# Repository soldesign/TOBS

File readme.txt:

Currently, 1.3 billion people live without access to electricity. Most of them are inhabitants of rural regions in developing south, that don’t have connection to the electricity grid. 
Fortunately, clean energy technologies have been reaching these people more and more in the past years. Mostly, but not only, in Bangladesh, a renewable energy revolution is taking place: the emergence of small scale solar-home-systems that supply electricity for lighting, cellphones and household appliances - in Bangladesh alone, there are already over 5 million solar-home-systems installed! These system feature a small PV panel with a charging controller and a battery (The solar home systems are usually financed with a micro loan from a microfinance institution, because its owner sometimes earn as little as one dollar per day).

To cut costs in these systems, lead-acid batteries are usually installed. Unfortunately, lead-acid batteries have a limited number of charge-discharge-cycles, much less than, for example, modern LIFEPO batteries. Also, they age quickly if they are discharged below around 40% of their capacity. This leads to many of the batteries breaking within 2 years or less, rendering the solar home systems unusable.

Moreover, as developing countries don’t have proficient infrastructure to dispose or recycle the lead-acid batteries, each failing battery leads to waste of resources and significant environmental pollution.

>lead acid batties are vulnurable to cycling often

How to solve the problem?

-retrofitting hybrid charge controller!

Using LIFEPO based batteries would significantly increase the solar home system’s lifetime­, as LIFEPO batteries are less affected by cycling compared to lead-acid batteries. However, initial high investment costs for LIFEPO batteries are often not feasible for developing markets. To get the best of both, a hybrid charge controller which supports a small lithium-ion battery and a bigger lead-acid battery simultaneously, would be ideal.

> LIFEPO batteries are better but too expensive 

A normal charge controller is responsible for monitoring the battery’s voltage and for controlling the charge and discharge cycle. In comparison, a hybrid charge controller would be able to switch between the two battery types, considering environmental factors, such as load current, solar irradiance and state of charge of both batteries. This will result in the li-ion battery having a smaller capacity, therefore cutting its cost. An algorithm would then only use the lead acid battery if the load is too big for the lithium ion battery to handle. For smaller loads and thus more cycles, the lithium ion battery would be used.

> lead acid battery will be cycled less often

Thus, the new hybrid charge controller aims to prolong the lifespan of millions of already existing lead acid batteries inside solar home systems by reducing sulfuration.

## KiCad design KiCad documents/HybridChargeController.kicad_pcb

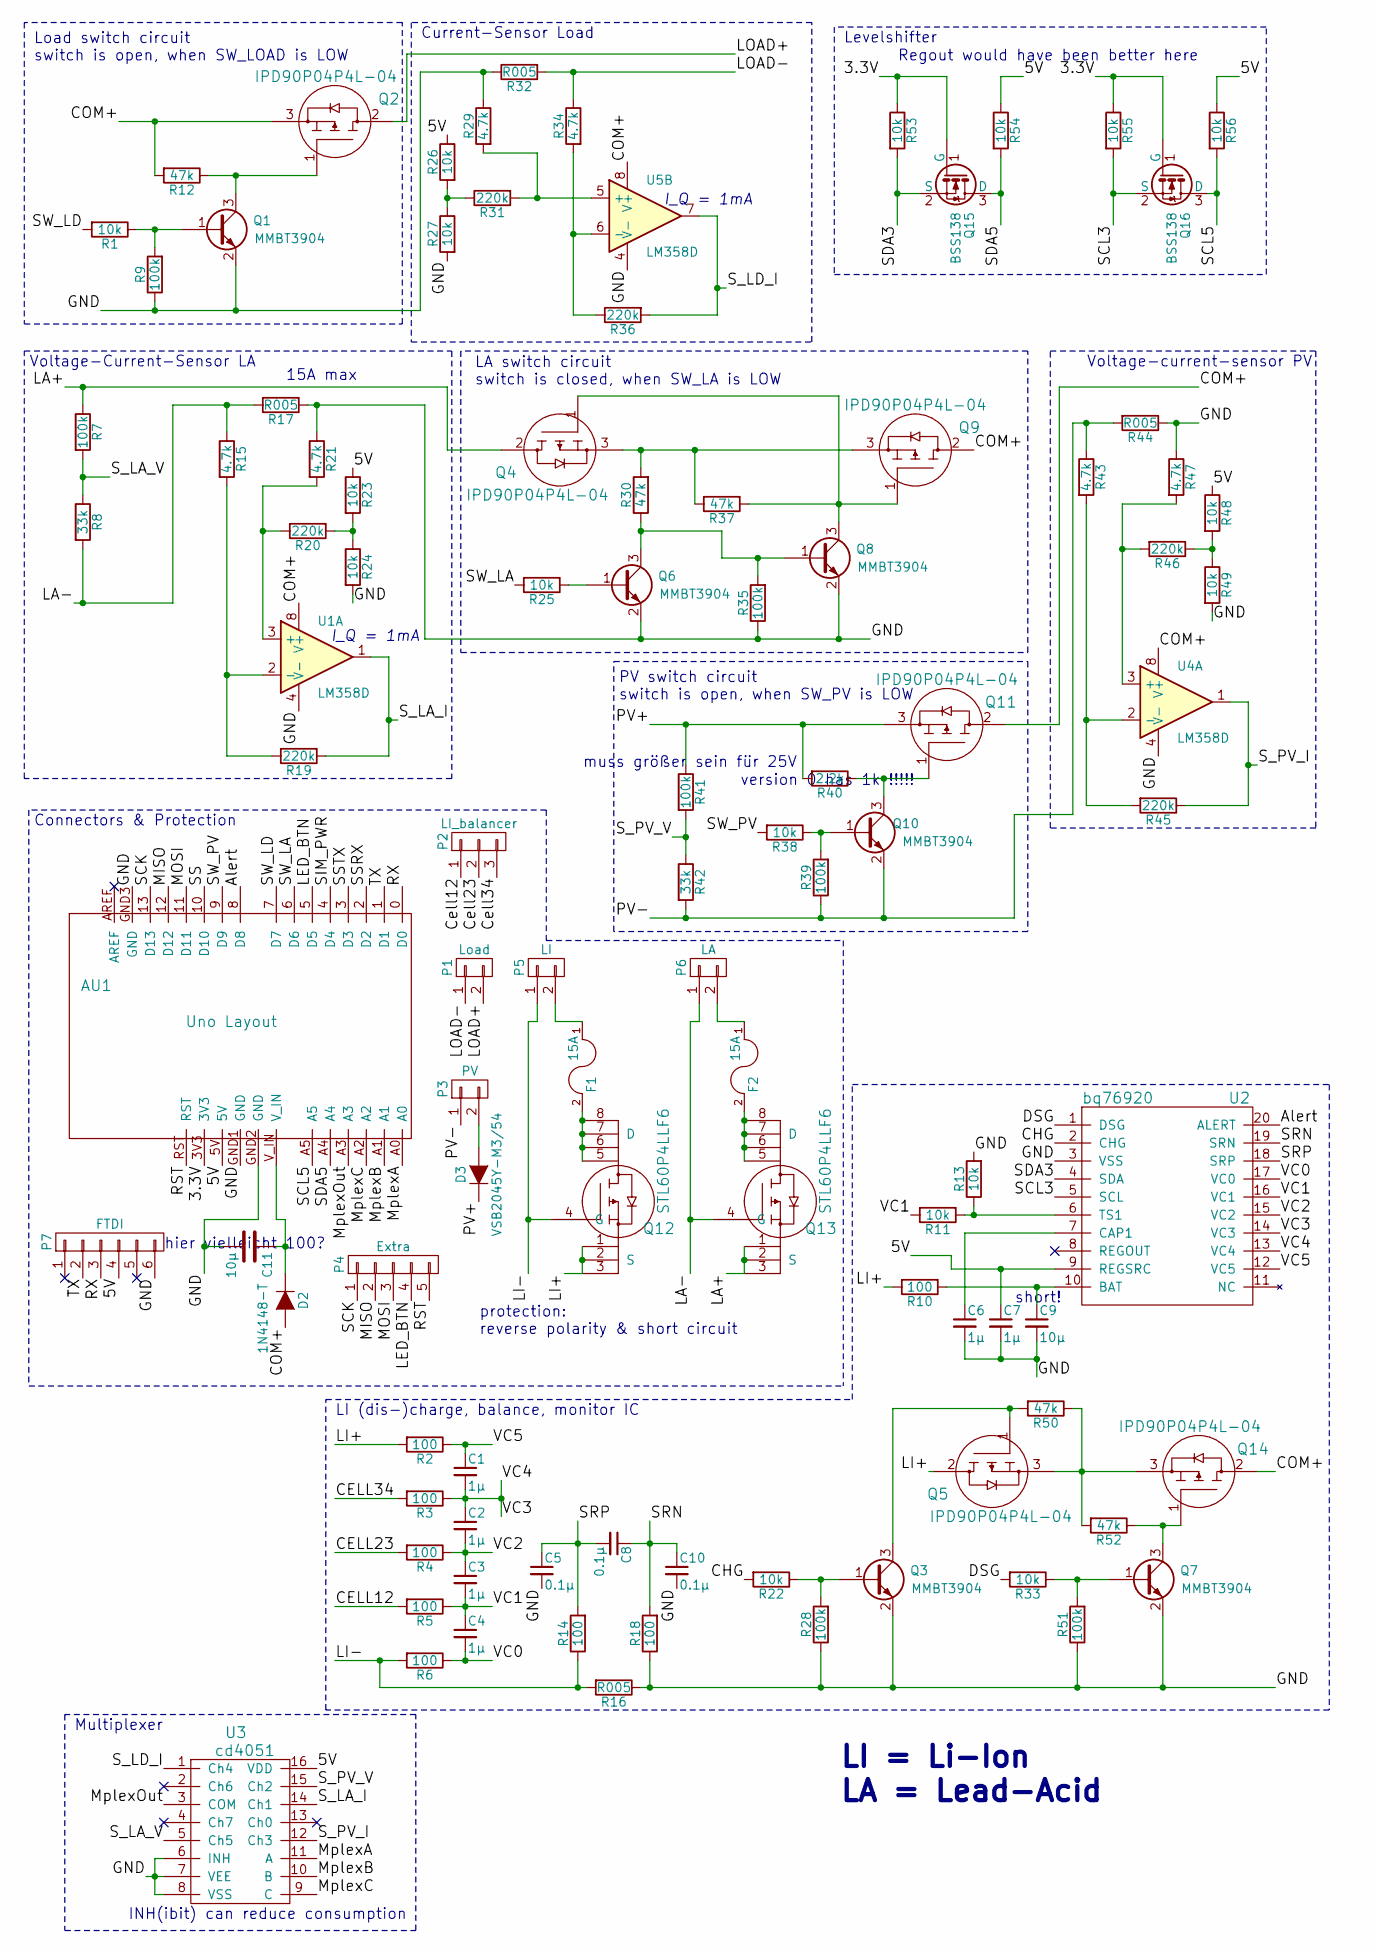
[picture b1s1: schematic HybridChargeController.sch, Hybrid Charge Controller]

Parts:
AU1: Uno Layout; ARDUINO_SHIELD_bigger_holes_no_outline
C1, C2, C3, C4, C6, C7: 1µ; C_0603_HandSoldering
C5, C8, C10: 0.1µ; C_0603_HandSoldering
C9, C11: 10µ; CP_Radial_D5.0mm_P2.00mm
D2: 1N4148-T; D_DO-35_SOD27_P10.16mm_Horizontal
D3: VSB2045Y-M3/54; D_P600_R-6_P12.70mm_Horizontal
F1, F2: 15A; Fuse_SMD1206_HandSoldering
P1: Load; TerminalBlock_Screw_2pol
P2: LI_balancer; Pin_Header_Straight_1x03_Pitch2.54mm
P3: PV; TerminalBlock_Screw_2pol
P4: Extra; Pin_Header_Straight_1x05_Pitch2.54mm
P5: LI; TerminalBlock_Screw_2pol
P6: LA; TerminalBlock_Screw_2pol
P7: FTDI; Pin_Header_Straight_1x06_Pitch2.54mm
Q1, Q3, Q6, Q7, Q8, Q10: MMBT3904; SOT-23
Q2, Q4, Q5, Q9, Q11, Q14: IPD90P04P4L-04; TO-252-3_TabPin2
Q12, Q13: STL60P4LLF6; powerFLAT_5x6_5..8com
Q15, Q16: BSS138; SOT-23
R1, R11, R13, R22, R23, R24, R25, R26, R27, R33, R38, R48, R49, R53, R54, R55, R56: 10k; R_0603_HandSoldering
R2, R3, R4, R5, R6, R10, R14, R18: 100; R_0603_HandSoldering
R7, R9, R28, R35, R39, R41, R51: 100k; R_0603_HandSoldering
R8, R42: 33k; R_0603_HandSoldering
R12, R30, R37, R50, R52: 47k; R_0603_HandSoldering
R15, R21, R29, R34, R43, R47: 4.7k; R_0603_HandSoldering
R16, R17, R32, R44: R005; R_1206_HandSoldering
R19, R20, R31, R36, R45, R46: 220k; R_0603_HandSoldering
R40: 2.2k; R_0603_HandSoldering
U1, U4, U5: LM358D; SOIC-8-N
U2: bq76920; SSOP-20
U3: cd4051; SO-16-N

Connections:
/3.3V: AU1.3V3, Q15.1 (G), Q16.1 (G), R53.1, R55.1
/5V: AU1.5V, C7.1, P7.4, R23.1, R26.1, R48.1, R54.1, R56.1, U2.9 (REGSRC), U3.16 (VDD)
/Alert: AU1.8 (D8), U2.20 (ALERT)
/CELL12: P2.1, R5.2
/CELL23: P2.2, R4.2
/CELL34: P2.3, R3.2
/CHG: R22.2, U2.2 (CHG)
/COM+: D2.2 (A), Q2.3, Q9.2, Q11.2, Q14.2, R12.2, U1.8 (V+), U4.8 (V+), U5.8 (V+)
/DSG: R33.2, U2.1 (DSG)
/GND: AU1.GND1 (GND), AU1.GND2 (GND), AU1.GND3 (GND), C5.2, C6.2, C7.2, C9.2, C10.2, C11.2, P7.6, Q1.2 (E), Q3.2 (E), Q6.2 (E), Q7.2 (E), Q8.2 (E), R9.1, R13.2, R16.1, R17.1, R18.1, R21.1, R24.2, R27.2, R28.1, R29.1, R32.1, R35.1, R44.1, R47.1, R49.2, R51.1, U1.4 (V-), U2.3 (VSS), U3.6 (INH), U3.7 (VEE), U3.8 (VSS), U4.4 (V-), U5.4 (V-)
/LA+: Q4.2, Q13.1, Q13.2 (S), Q13.3, R7.1
/LA-: P6.1, Q13.4 (G), R8.2, R15.1, R17.2
/LED_BTN: AU1.5 (D5), P4.4
/LI+: Q5.2, Q12.1, Q12.2 (S), Q12.3, R2.2, R10.2
/LI-: P5.1, Q12.4 (G), R6.2, R14.1, R16.2
/LOAD+: P1.2, Q2.2
/LOAD-: P1.1, R32.2, R34.1
/MISO: AU1.12 (D12), P4.2
/MOSI: AU1.11 (D11), P4.3
/MplexA: AU1.A0, U3.11 (A)
/MplexB: AU1.A1, U3.10 (B)
/MplexC: AU1.A2, U3.9 (C)
/MplexOut: AU1.A3, U3.3 (COM)
/PV+: D3.1 (K), Q11.3, R40.2, R41.1
/PV-: P3.1, Q10.2 (E), R39.1, R42.2, R43.1, R44.2
/RST: AU1.RST, P4.5
/RX: AU1.0 (D0), P7.3
/SCK: AU1.13 (D13), P4.1
/SCL3: Q16.2 (S), R55.2, U2.5 (SCL)
/SCL5: AU1.A5, Q16.3 (D), R56.2
/SDA3: Q15.2 (S), R53.2, U2.4 (SDA)
/SDA5: AU1.A4, Q15.3 (D), R54.2
/SIM_PWR: AU1.4 (D4)
/SRN: C8.1, C10.1, R18.2, U2.19 (SRN)
/SRP: C5.1, C8.2, R14.2, U2.18 (SRP)
/SS: AU1.10 (D10)
/SSRX: AU1.2 (D2)
/SSTX: AU1.3 (D3)
/SW_LA: AU1.6 (D6), R25.2
/SW_LD: AU1.7 (D7), R1.2
/SW_PV: AU1.9 (D9), R38.2
/S_LA_I: R19.1, U1.1, U3.14 (Ch1)
/S_LA_V: R7.2, R8.1, U3.5 (Ch5)
/S_LD_I: R36.2, U3.1 (Ch4), U5.7
/S_PV_I: R45.1, U3.12 (Ch3), U4.1
/S_PV_V: R41.2, R42.1, U3.15 (Ch2)
/TX: AU1.1 (D1), P7.2
/VC0: C4.2, R6.1, U2.17 (VC0)
/VC1: C3.2, C4.1, R5.1, R11.2, U2.16 (VC1)
/VC2: C2.2, C3.1, R4.1, U2.15 (VC2)
/VC3: C1.2, C2.1, R3.1, U2.13 (VC4), U2.14 (VC3)
/VC5: C1.1, R2.1, U2.12 (VC5)
unnamed: AU1.V_IN, C11.1, D2.1 (K)
unnamed: C6.1, U2.7 (CAP1)
unnamed: C9.1, R10.1, U2.10 (BAT)
unnamed: D3.2 (A), P3.2
unnamed: F1.1, P5.2
unnamed: F1.2, Q12.5, Q12.6, Q12.7 (D), Q12.8
unnamed: F2.1, P6.2
unnamed: F2.2, Q13.5, Q13.6, Q13.7 (D), Q13.8
unnamed: Q1.1 (B), R1.1, R9.2
unnamed: Q1.3 (C), Q2.1, R12.1
unnamed: Q3.1 (B), R22.1, R28.2
unnamed: Q3.3 (C), Q5.1, R50.2
unnamed: Q4.1, Q8.3 (C), Q9.1, R37.1
unnamed: Q4.3, Q9.3, R30.2, R37.2
unnamed: Q6.1 (B), R25.1
unnamed: Q6.3 (C), Q8.1 (B), R30.1, R35.2
unnamed: Q7.1 (B), R33.1, R51.2
unnamed: Q10.1 (B), R38.1, R39.2
unnamed: Q10.3 (C), Q11.1, R40.1
unnamed: Q7.3 (C), Q14.1, R52.1
unnamed: Q5.3, Q14.3, R50.1, R52.2
unnamed: R11.1, R13.1, U2.6 (TS1)
unnamed: R15.2, R19.2, U1.2 (-)
unnamed: R20.1, R23.2, R24.1
unnamed: R20.2, R21.2, U1.3 (+)
unnamed: R26.2, R27.1, R31.1
unnamed: R29.2, R31.2, U5.5 (+)
unnamed: R34.2, R36.1, U5.6 (-)
unnamed: R43.2, R45.2, U4.2 (-)
unnamed: R46.1, R48.2, R49.1
unnamed: R46.2, R47.2, U4.3 (+)

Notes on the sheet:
LA switch circuit switch is closed, when SW_LA is LOW
Load switch circuit switch is open, when SW_LOAD is LOW
Voltage-Current-Sensor LA
Current-Sensor Load
Voltage-current-sensor PV
Connectors & Protection
PV switch circuit switch is open, when SW_PV is LOW
LI = Li-Ion LA = Lead-Acid
I_Q = 1mA
LI (dis-)charge, balance, monitor IC
INH(ibit) can reduce consumption
Multiplexer
protection: reverse polarity & short circuit
15A max
short!
Levelshifter
Regout would have been better here
hier vielleicht 100?
muss größer sein für 25V
version 0 has 1k !!!!!

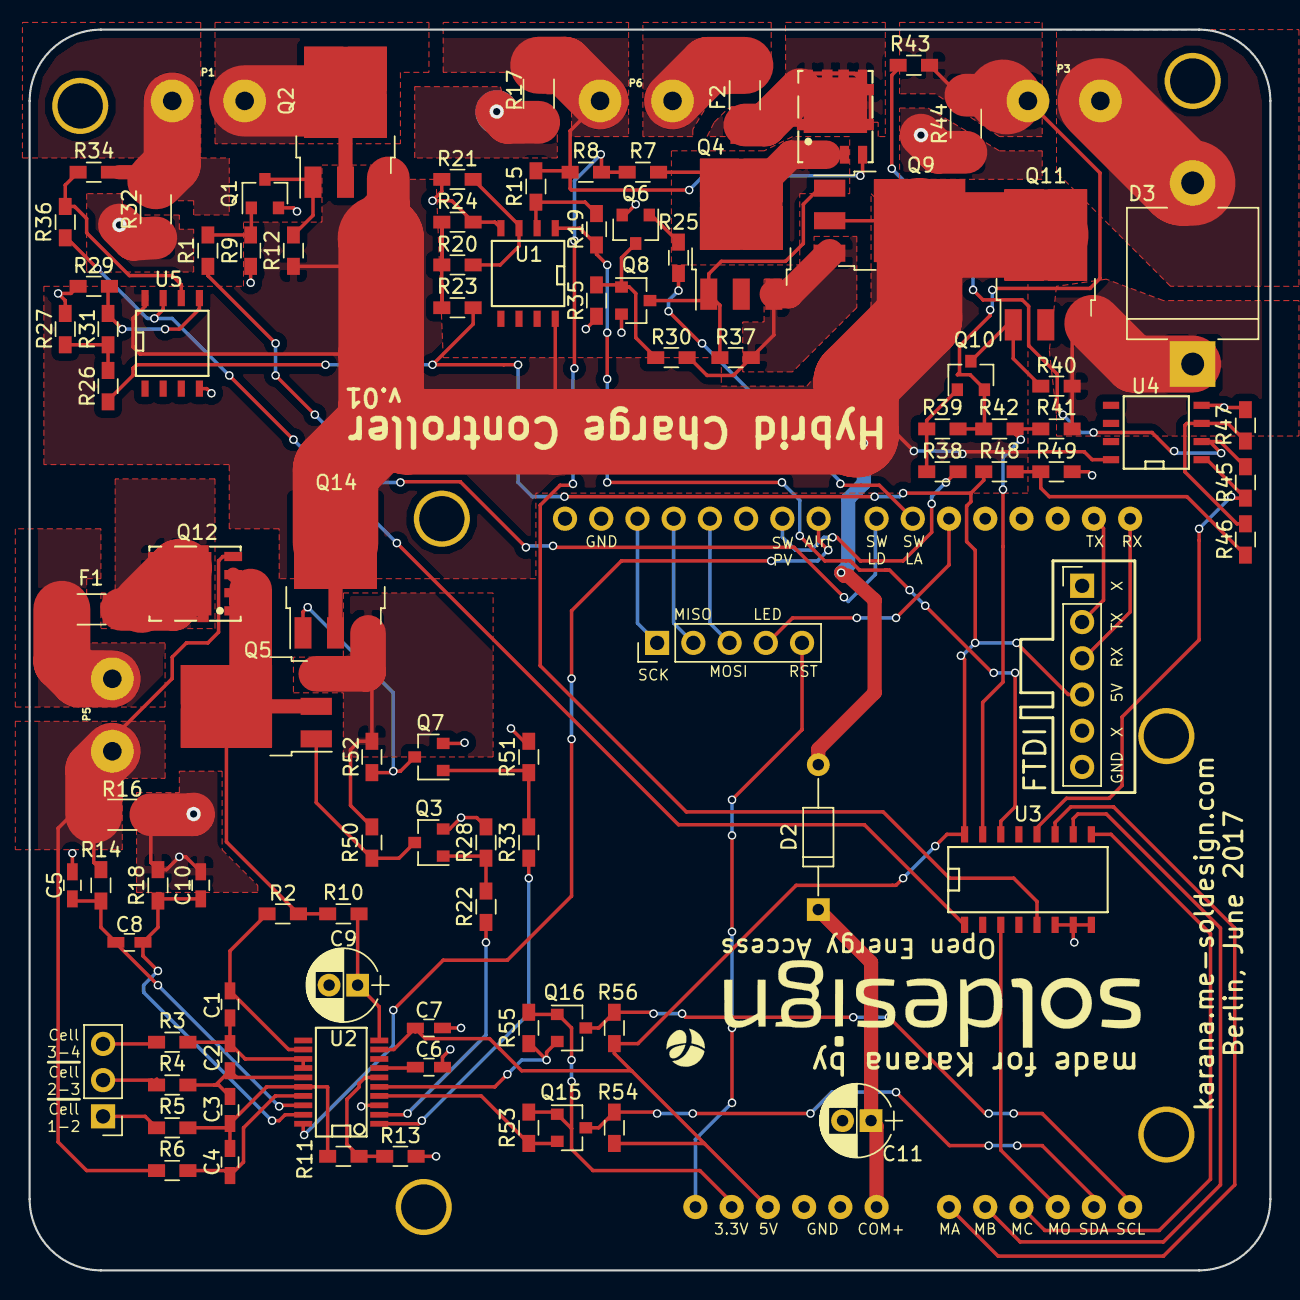
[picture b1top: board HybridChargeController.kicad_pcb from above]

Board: 2 copper layers, 87.0 x 87.0 mm, 100 parts (0 on the bottom side), 79 nets.

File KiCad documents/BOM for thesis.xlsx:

Quantity | Value | Type | Price (10) | Price (100) | Reihenfolge | summ10 | summe100
1 | BQ76920 | Balancer | 2.87 | 2.77 | 1 | 2.87 | 2.77
1 | CD4051 | Multiplexer | 0.3 | 0.183 | 2 | 0.3 | 0.183
6 | IPD90P04P4L-04 | Power MOSFET | 1.1499999999999999 | 0.875 | 3 | 6.8999999999999995 | 5.25
2 | STL60P4LLF6 | MOSFET | 0.69199999999999995 | 0.53200000000000003 | 4 | 1.3839999999999999 | 1.0640000000000001
2 | BSS138 | Logic MOSFET | 0.159 | 6.6000000000000003E-2 | 5 | 0.318 | 0.13200000000000001
6 | MMBT3904 | Logic transistor | 0.16 | 0.14000000000000001 | 6 | 0.96 | 0.84000000000000008
1 | VSB2045Y-M3/54 | Schottky | 0.96699999999999997 | 0.82899999999999996 | 7 | 0.96699999999999997 | 0.82899999999999996
1 | 1N4148-T | Diode | 2.1999999999999999E-2 | 1.7999999999999999E-2 | 8 | 2.1999999999999999E-2 | 1.7999999999999999E-2
3 | LM358D | Op-Amp | 0.26600000000000001 | 0.14399999999999999 | 9 | 0.79800000000000004 | 0.43199999999999994
2 | 15A | Fuse |  |  | 10 | 0 | 0
4 | R005 | Shunt |  |  | 11 | 0 | 0
6 | 220k | Resistor |  |  | 12 | 0 | 0
7 | 100k | Resistor |  |  | 13 | 0 | 0
5 | 47k | Resistor |  |  | 14 | 0 | 0
2 | 33k | Resistor |  |  | 15 | 0 | 0
17 | 10k | Resistor |  |  | 16 | 0 | 0
6 | 4.7k | Resistor |  |  | 17 | 0 | 0
1 | 2.2k | Resistor |  |  | 18 | 0 | 0
8 | 100 | Resistor |  |  | 19 | 0 | 0
2 | 10µ | Capacitor |  |  | 20 | 0 | 0
6 | 1µ | Capacitor |  |  | 21 | 0 | 0
3 | 0.1µ | Capacitor |  |  | 22 | 0 | 0
4 | 5mm pitch | Screw Terminal | 0.24 | 0.2 | 23 | 0.96 | 0.8
1 | 1x6 female | Pin header | 0.26 | 0.23 | 24 | 0.26 | 0.23
2 | 1x8 male | Pin header | 0.22 | 0.2 | 25 | 0.44 | 0.4
2 | 1x6 male | Pin header | 0.16 | 0.13 | 26 | 0.32 | 0.26
1 | 1x3 male | Pin header | 0.08 | 0.06 | 27 | 0.08 | 0.06
 |  | Sum | 16.578999999999997 | 13.268000000000002 |  | 16.578999999999997 | 13.268000000000002

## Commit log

2017-03-23 created Kicad project
2017-03-27 switching mechanism ready to test
2017-03-27 switched to transistors maybe need 10k
2017-04-05 two mosfets on both power lines. working nicely
2017-04-12 added readme
2017-04-12 added arduinouno footprint
2017-04-12 added two sensor circuits
2017-04-12 added vcs PV and connectors
2017-04-19 no changes?
2017-04-19 added only some comments and open questions for discussion
2017-04-19 new pseudo schematic
2017-04-21 added LI IC, removed own LI circuit part
2017-04-26 added multiplexer
2017-04-27 added protections
2017-04-27 selfmade STL60P4LLF6
2017-04-27 added extra connections
2017-04-27 order ready
2017-05-09 added more footprints
2017-05-09 more and more footprints
2017-05-09 started pcb
2017-05-10 noticed low side switching
2017-05-16 going to switch on high side
2017-05-16 new branch highside switch
2017-05-16 implemented new HS switch
2017-05-16 startet distributing components
2017-05-16 completed vaguely arranging footprints
2017-05-17 power paths done
2017-05-17 more traces done
2017-05-18 almost all tracks done
2017-05-18 ready for review
2017-05-21 added a few comments for final check, played with the Silkscreen a bit
2017-05-22 added FTDI connector
2017-05-22 gerbered like this
2017-05-23 new gerber files
2017-05-23 added ino file and NOTICED MISTAKE IN KICAT PIN 8 X 9
2017-05-23 switched 8 and 9 and hope for the best
2017-05-24 need to find out why there are extra headers
2017-05-24 fixed extra holes, send new gerbers
2017-06-05 going to put schematic on A4
2017-06-06 sucessfully migrated to A4 for schematic
2017-06-15 played around with i2c
2017-06-19 added explanations schematic
2017-06-28 ready for ordering pt 2
2017-07-11 will alter PI controller into struct
2017-07-11 pi solved, problem with balancer
2017-07-11 checking out what was altered
2017-07-11 dont know what was wrong, everything is working now
2017-07-11 end of day
2017-07-12 simple cc
2017-07-12 deleted LOWDISCON states
2017-07-13 Add license
2017-07-13 first tests
2017-07-14 going to check if actually charging at charge protocol
2017-07-14 trying PID library again
2017-07-15 going to strip down loop for pid calibration
2017-07-15 new controller works, trying to get rid of spikes
2017-07-16 going to try less delay between measurements
2017-07-19 last version of code before handing in thesis
